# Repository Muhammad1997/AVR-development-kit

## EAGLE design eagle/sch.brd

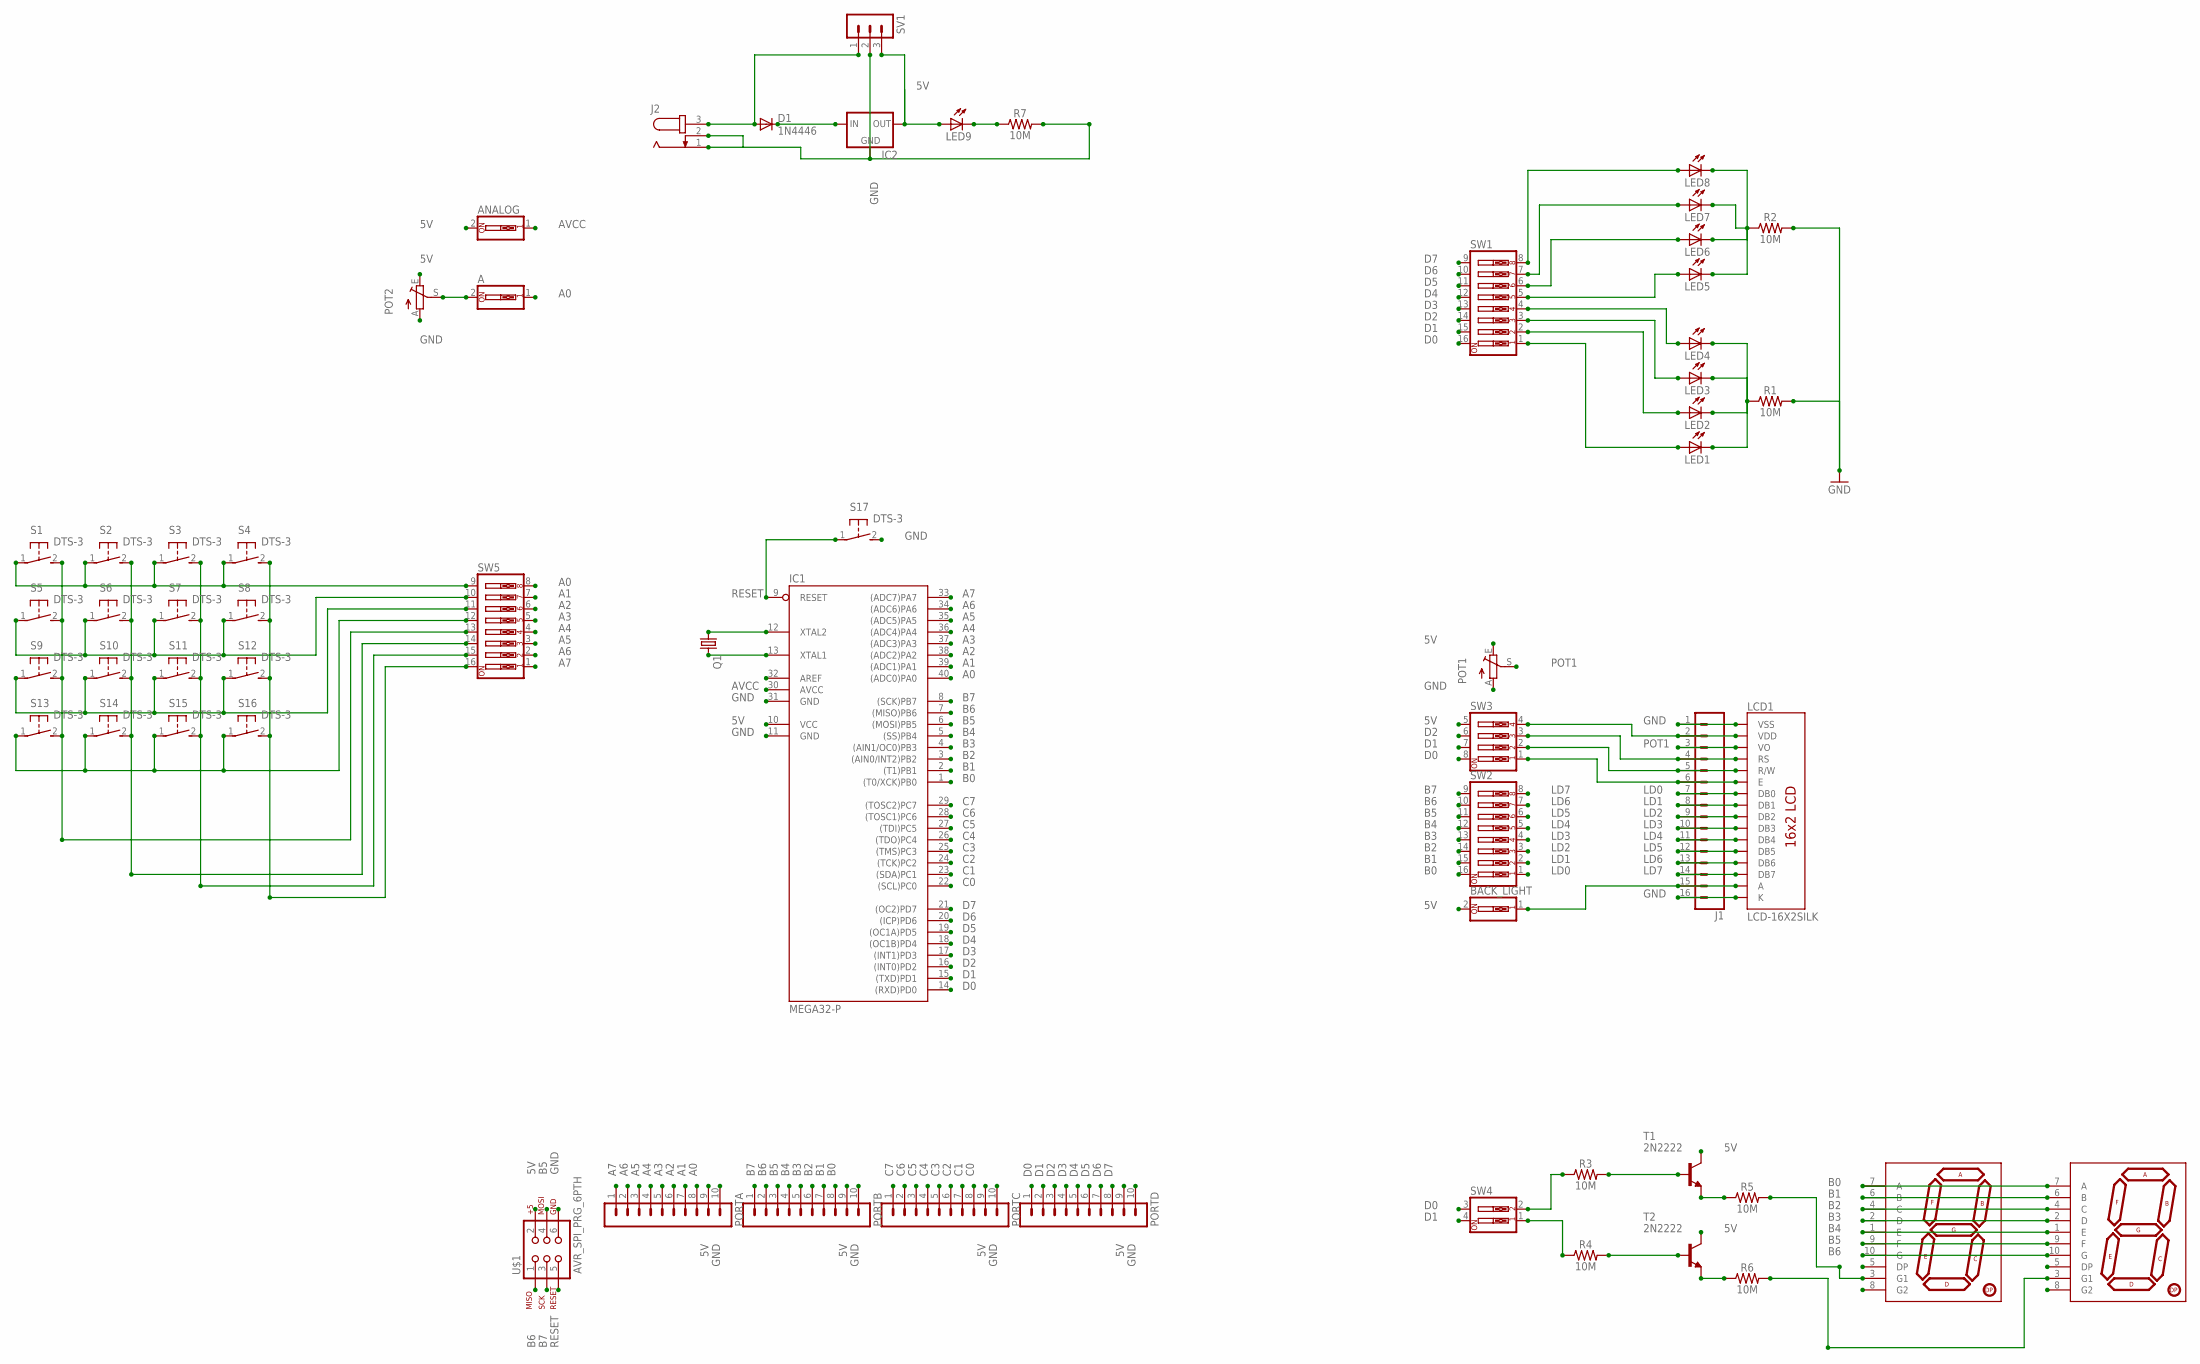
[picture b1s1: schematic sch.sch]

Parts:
A: SW_DIP-1; EDG-01
ANALOG: SW_DIP-1; EDG-01
BACK_LIGHT: SW_DIP-1; EDG-01
D1: 1N4446; DO35-10
IC1: MEGA32-P; DIL40
IC2: 78MXXL
J1: CONN_16LONGPADS; 1X16_LONGPADS
J2: JACK-PLUG0; SPC4077
LCD1: LCD-16X2SILK; LCD-16X2
LED1, LED2, LED3, LED4, LED5, LED6, LED7, LED8, LED9: LED5MM
PORTA: MA10-1
PORTB: MA10-1
PORTC: MA10-1
PORTD: MA10-1
POT1, POT2: TRIM_EU-B25P; B25P
Q1: CRYTALHC49U-V; HC49U-V
R1, R2, R3, R4, R5, R6, R7: 10M; AXIAL-0.3
S1, S2, S3, S4, S5, S6, S7, S8, S9, S10, S11, S12, S13, S14, S15, S16, S17: DTS-3
SV1: MA03-1
SW1, SW2, SW5: SW_DIP-8; EDG-08
SW3: SW_DIP-4; EDG-04
SW4: SW_DIP-2; DIPSWITCH-02
T1, T2: 2N2222; TO92-EBC-OVAL
U$1: AVR_SPI_PRG_6PTH; 2X3
U$2, U$3: YSD-160AB3C-8; 7-SEGMENT-1"PTH-EZ

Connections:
5V: ANALOG.2, BACK_LIGHT.2, IC1.10 (VCC), IC2.OUT, LED9.A, PORTA.9, PORTB.9, PORTC.9, PORTD.9, POT1.E, POT2.E, SV1.3, SW3.5, T1.C, T2.C, U$1.2
A0: A.1, IC1.40 ((ADC0)PA0), PORTA.8, SW5.8
A1: IC1.39 ((ADC1)PA1), PORTA.7, SW5.7
A2: IC1.38 ((ADC2)PA2), PORTA.6, SW5.6
A3: IC1.37 ((ADC3)PA3), PORTA.5, SW5.5
A4: IC1.36 ((ADC4)PA4), PORTA.4, SW5.4
A5: IC1.35 ((ADC5)PA5), PORTA.3, SW5.3
A6: IC1.34 ((ADC6)PA6), PORTA.2, SW5.2
A7: IC1.33 ((ADC7)PA7), PORTA.1, SW5.1
AVCC: ANALOG.1, IC1.30 (AVCC)
B0: IC1.1 ((T0/XCK)PB0), PORTB.8, SW2.16, U$2.7 (A), U$3.7 (A)
B1: IC1.2 ((T1)PB1), PORTB.7, SW2.15, U$2.6 (B), U$3.6 (B)
B2: IC1.3 ((AIN0/INT2)PB2), PORTB.6, SW2.14, U$2.4 (C), U$3.4 (C)
B3: IC1.4 ((AIN1/OC0)PB3), PORTB.5, SW2.13, U$2.2 (D), U$3.2 (D)
B4: IC1.5 ((SS)PB4), PORTB.4, SW2.12, U$2.1 (E), U$3.1 (E)
B5: IC1.6 ((MOSI)PB5), PORTB.3, SW2.11, U$1.4, U$2.9 (F), U$3.9 (F)
B6: IC1.7 ((MISO)PB6), PORTB.2, SW2.10, U$1.1, U$2.10 (G), U$3.10 (G)
B7: IC1.8 ((SCK)PB7), PORTB.1, SW2.9, U$1.3
C0: IC1.22 ((SCL)PC0), PORTC.8
C1: IC1.23 ((SDA)PC1), PORTC.7
C2: IC1.24 ((TCK)PC2), PORTC.6
C3: IC1.25 ((TMS)PC3), PORTC.5
C4: IC1.26 ((TDO)PC4), PORTC.4
C5: IC1.27 ((TDI)PC5), PORTC.3
C6: IC1.28 ((TOSC1)PC6), PORTC.2
C7: IC1.29 ((TOSC2)PC7), PORTC.1
D0: IC1.14 ((RXD)PD0), PORTD.1, SW1.16, SW3.8, SW4.3
D1: IC1.15 ((TXD)PD1), PORTD.2, SW1.15, SW3.7, SW4.4
D2: IC1.16 ((INT0)PD2), PORTD.3, SW1.14, SW3.6
D3: IC1.17 ((INT1)PD3), PORTD.4, SW1.13
D4: IC1.18 ((OC1B)PD4), PORTD.5, SW1.12
D5: IC1.19 ((OC1A)PD5), PORTD.6, SW1.11
D6: IC1.20 ((ICP)PD6), PORTD.7, SW1.10
D7: IC1.21 ((OC2)PD7), PORTD.8, SW1.9
GDHJH: R4.P$1 (1), SW4.1
GFHGV: R3.P$1 (1), SW4.2
GND: IC1.11 (GND), IC1.31 (GND), IC2.GND, J1.1, J1.16, J2.1, J2.2, LCD1.1 (VSS), LCD1.16 (K), PORTA.10, PORTB.10, PORTC.10, PORTD.10, POT1.A, POT2.A, R1.P$2 (2), R2.P$2 (2), R7.P$2 (2), S17.2, SV1.2, U$1.6
LD0: J1.7, LCD1.7 (DB0), SW2.1
LD1: J1.8, LCD1.8 (DB1), SW2.2
LD2: J1.9, LCD1.9 (DB2), SW2.3
LD3: J1.10, LCD1.10 (DB3), SW2.4
LD4: J1.11, LCD1.11 (DB4), SW2.5
LD5: J1.12, LCD1.12 (DB5), SW2.6
LD6: J1.13, LCD1.13 (DB6), SW2.7
LD7: J1.14, LCD1.14 (DB7), SW2.8
unnamed: LED1.K (C), LED2.K (C), LED3.K (C), LED4.K (C), R1.P$1 (1)
unnamed: R6.P$2 (2), U$3.3 (G1)
unnamed: R3.P$2 (2), T1.B
unnamed: J1.4, LCD1.4 (RS), SW3.3
unnamed: J1.5, LCD1.5 (R/W), SW3.2
unnamed: J1.6, LCD1.6 (E), SW3.1
unnamed: LED5.K (C), LED6.K (C), LED7.K (C), LED8.K (C), R2.P$1 (1)
unnamed: D1.A, J2.3, SV1.1
unnamed: R5.P$1 (1), T1.E
unnamed: R6.P$1 (1), T2.E
unnamed: S1.2, S5.2, S9.2, S13.2, SW5.13
unnamed: IC1.13 (XTAL1), Q1.2
unnamed: R4.P$2 (2), T2.B
unnamed: LED8.A, SW1.8
unnamed: LED7.A, SW1.7
unnamed: LED6.A, SW1.6
unnamed: LED5.A, SW1.5
unnamed: LED4.A, SW1.4
unnamed: LED3.A, SW1.3
unnamed: LED2.A, SW1.2
unnamed: LED1.A, SW1.1
unnamed: BACK_LIGHT.1, J1.15, LCD1.15 (A)
unnamed: S2.2, S6.2, S10.2, S14.2, SW5.14
unnamed: R5.P$2 (2), U$2.3 (G1)
unnamed: A.2, POT2.S
unnamed: S3.2, S7.2, S11.2, S15.2, SW5.15
unnamed: S1.1, S2.1, S3.1, S4.1, SW5.9
unnamed: D1.C, IC2.IN
unnamed: S4.2, S8.2, S12.2, S16.2, SW5.16
unnamed: IC1.12 (XTAL2), Q1.1
unnamed: LED9.K (C), R7.P$1 (1)
unnamed: S5.1, S6.1, S7.1, S8.1, SW5.10
unnamed: S9.1, S10.1, S11.1, S12.1, SW5.11
unnamed: S13.1, S14.1, S15.1, S16.1, SW5.12
POT1: J1.3, LCD1.3 (VO), POT1.S
RESET: IC1.9 (RESET), S17.1, U$1.5
RRR: J1.2, LCD1.2 (VDD), SW3.4

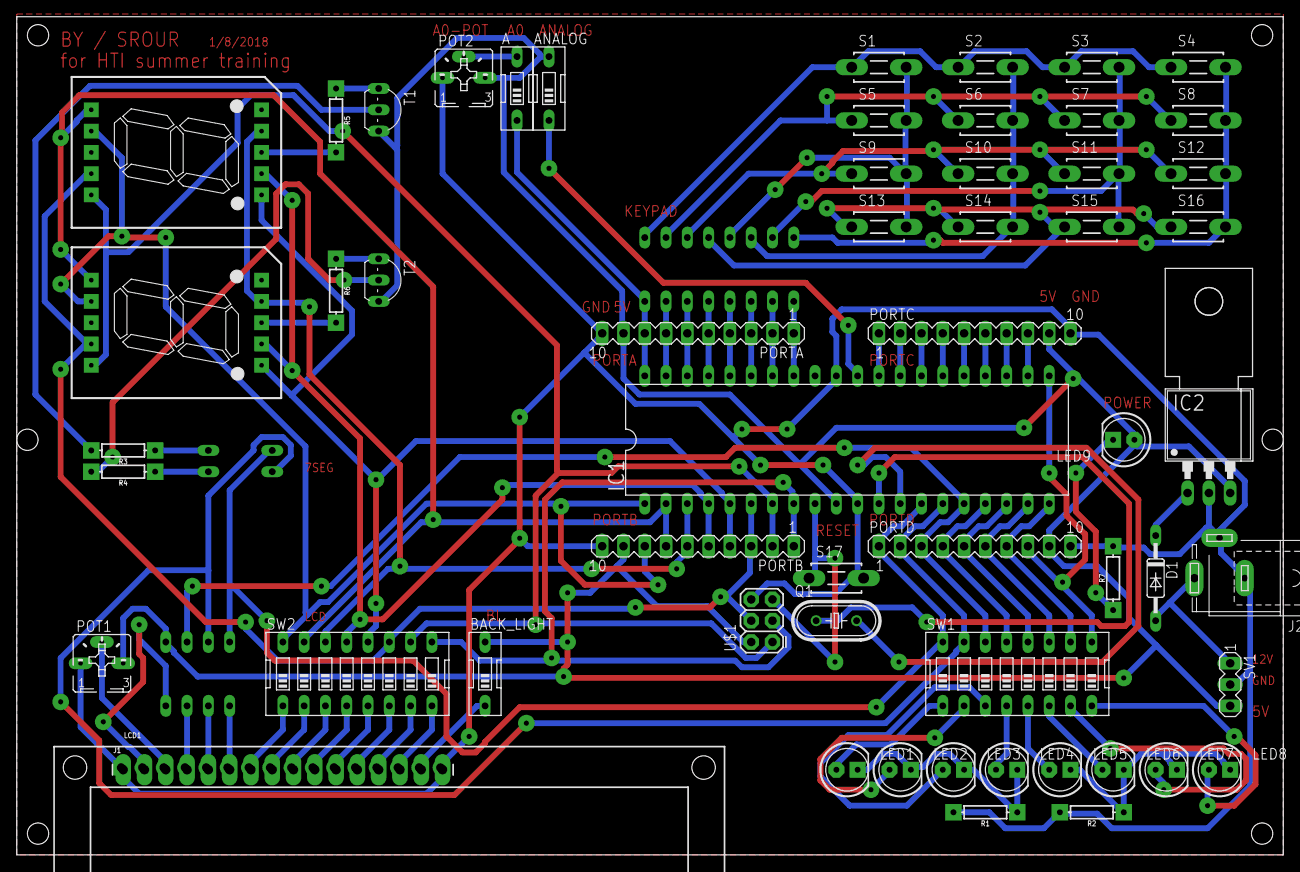
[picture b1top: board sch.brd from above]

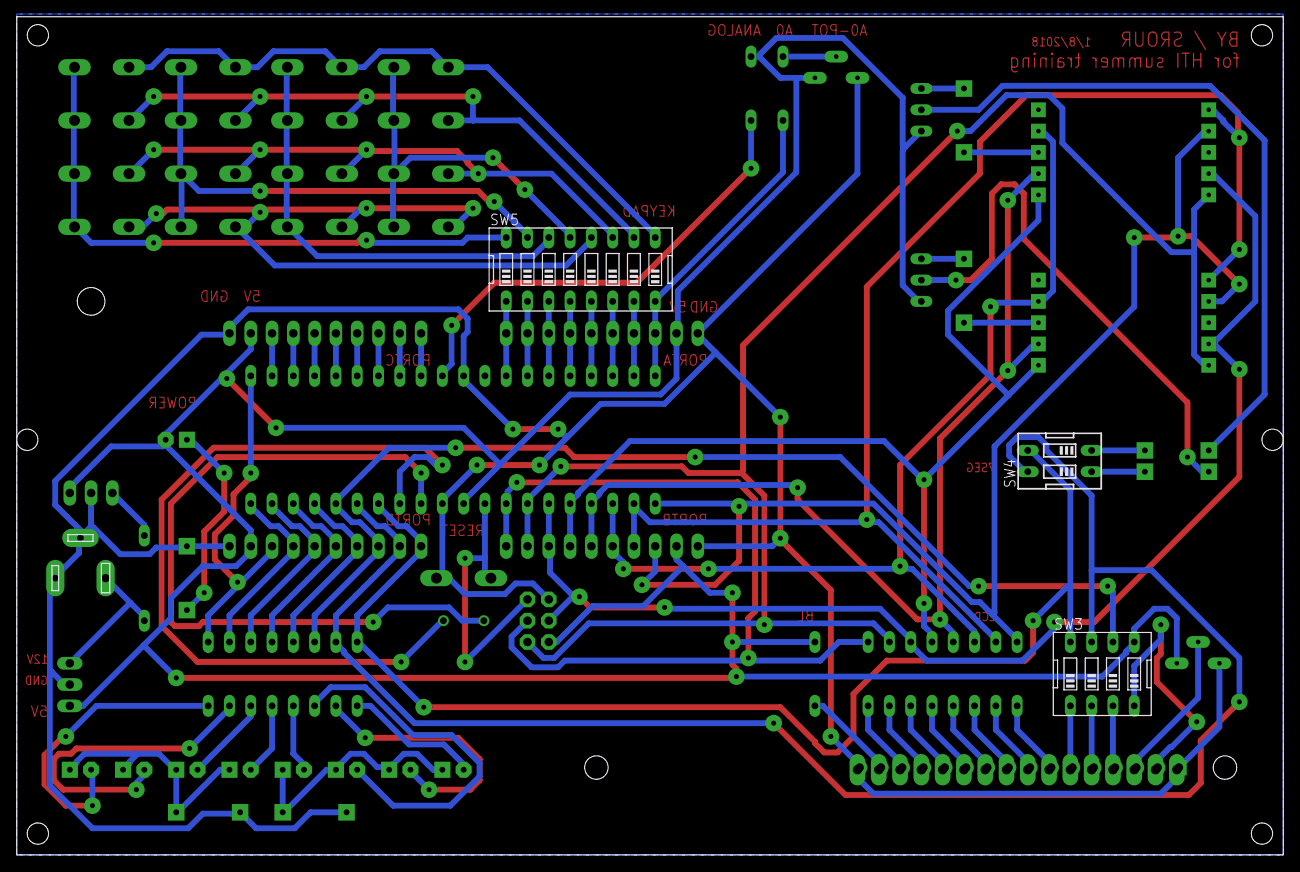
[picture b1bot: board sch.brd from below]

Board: 2 copper layers, 151.1 x 100.0 mm, 60 parts (3 on the bottom side), 82 nets.

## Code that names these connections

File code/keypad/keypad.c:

#define F_CPU 1000000UL
#include <avr/io.h>
#include <avr/delay.h>
char *key;
void keypad();
int main()
{
	DDRB = 0xff;
	DDRD = 0xff;
	DDRA = 0xf0;
	PORTA = 0x0f; //enable pull up res
    while (1) 
    {
		keypad();
		
    }
}

//keypad fun
void keypad (){
	//first row
	if (!(PINA & 1<<PA0))
	{
		PORTA |= 0b00010000;
		//first col
		if (PINA & 1<<PA0)
		{
			key = "1";
			PORTB = 0b00000001;
		}
		else {
			
			PORTA &= 0b11101111;
			PORTA |= 0b00100000;
			//2nd col
			if (PINA & 1<<PA0)
			{
				key = "2";
				PORTB = 0b00000010;
			}
			else{
				PORTA &= 0b11011111;
				PORTA |= 0b01000000;
				//3rd col
				if (PINA & 1<<PA0)
				{
					key = "3";
					PORTB = 0b00000100;
				}
				//4th col
				else
				{
					PORTA &= 0b10111111;
					PORTA |= 0b10000000;
					key = "4";
					PORTB = 0b00001000;
				}
				
				
			}
		}
	}
	
	//2nd row
	else if (!(PINA & 1<<PA1))
	{
		PORTA |= 0b00010000;
		//first col
		if (PINA & 1<<PA1)
		{
			key = "5";
			PORTB = 0b00010000;
		}
		else {
			
			PORTA &= 0b11101111;
			PORTA |= 0b00100000;
			//2nd col
			if (PINA & 1<<PA1)
			{
				key = "6";
				PORTB = 0b00100000;
			}
			else{
				PORTA &= 0b11011111;
				PORTA |= 0b01000000;
				//3rd col
				if (PINA & 1<<PA1)
				{
					key = "7";
					PORTB = 0b01000000;
				}
				//4th col
				else
				{
					PORTA &= 0b10111111;
					PORTA |= 0b10000000;
					key = "8";
					PORTB = 0b10000000;
				}
				
				
			}
		}
	}
	
	//3rd row
	else if (!(PINA & 1<<PA2))
	{
		PORTA |= 0b00010000;
		//first col
		if (PINA & 1<<PA2)
		{
			key = "9";
			PORTD = 0b00000001;
		}
		else {
			
			PORTA &= 0b11101111;
			PORTA |= 0b00100000;
			//2nd col
			if (PINA & 1<<PA2)
			{
				key = "10";
				PORTD = 0b00000010;
			}
			else{
				PORTA &= 0b11011111;
				PORTA |= 0b01000000;
				//3rd col
				if (PINA & 1<<PA2)
				{
					key = "11";
					PORTD = 0b00000100;
				}
				//4th col
				else
				{
					PORTA &= 0b10111111;
					PORTA |= 0b10000000;
					key = "12";
					PORTD = 0b00001000;
				}
				
				
			}
		}
	}
	
	//4th row
	else if (!(PINA & 1<<PA3))
	{
		PORTA |= 0b00010000;
		//first col
		if (PINA & 1<<PA3)
		{
			key = "13";
			PORTD = 0b00010000;
		}
		else {
			
			PORTA &= 0b11101111;
			PORTA |= 0b00100000;
			//2nd col
			if (PINA & 1<<PA3)
			{
				key = "14";
				PORTD = 0b00100000;
			}
			else{
				PORTA &= 0b11011111;
				PORTA |= 0b01000000;
				//3rd col
				if (PINA & 1<<PA3)
				{
					key = "15";
					PORTD = 0b01000000;
				}
				//4th col
				else
				{
					PORTA &= 0b10111111;
					PORTA |= 0b10000000;
					key = "16";
					PORTD = 0b10000000;
				}
				
				
			}
		}
	}
	PORTA &= 0b00001111;
	_delay_ms(50);
	PORTB = 0b00000000;
	PORTD = 0b00000000;

}

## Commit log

2018-07-20 lcd+7seg
2018-07-20 keypad
2018-07-31 sch_001
2018-08-01 board

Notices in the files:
parts and their libraries:
SparkFun-Resistors: Licensing: Creative Commons ShareAlike 4.0 International - https://creativecommons.org/licenses/by-sa/4.0
